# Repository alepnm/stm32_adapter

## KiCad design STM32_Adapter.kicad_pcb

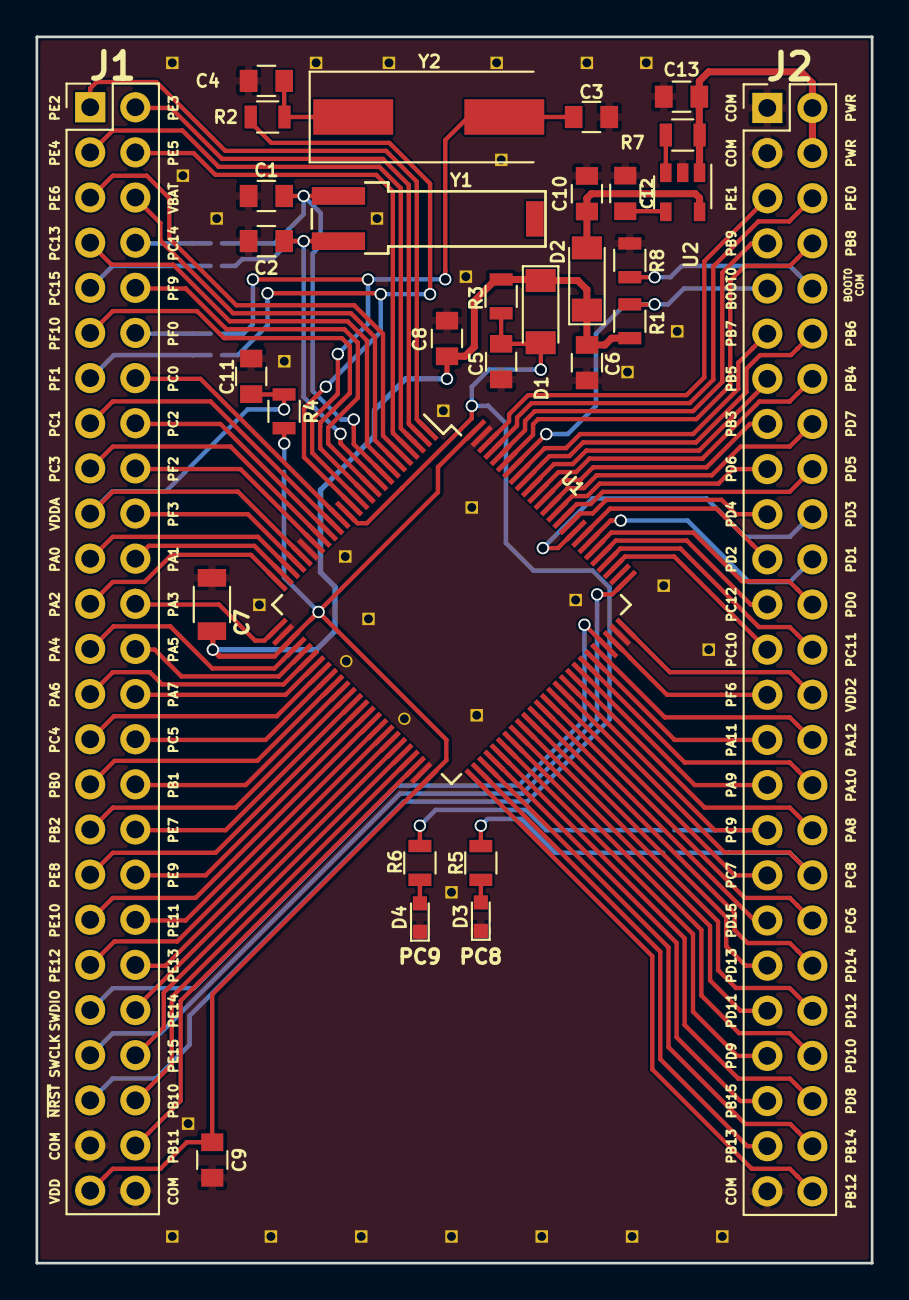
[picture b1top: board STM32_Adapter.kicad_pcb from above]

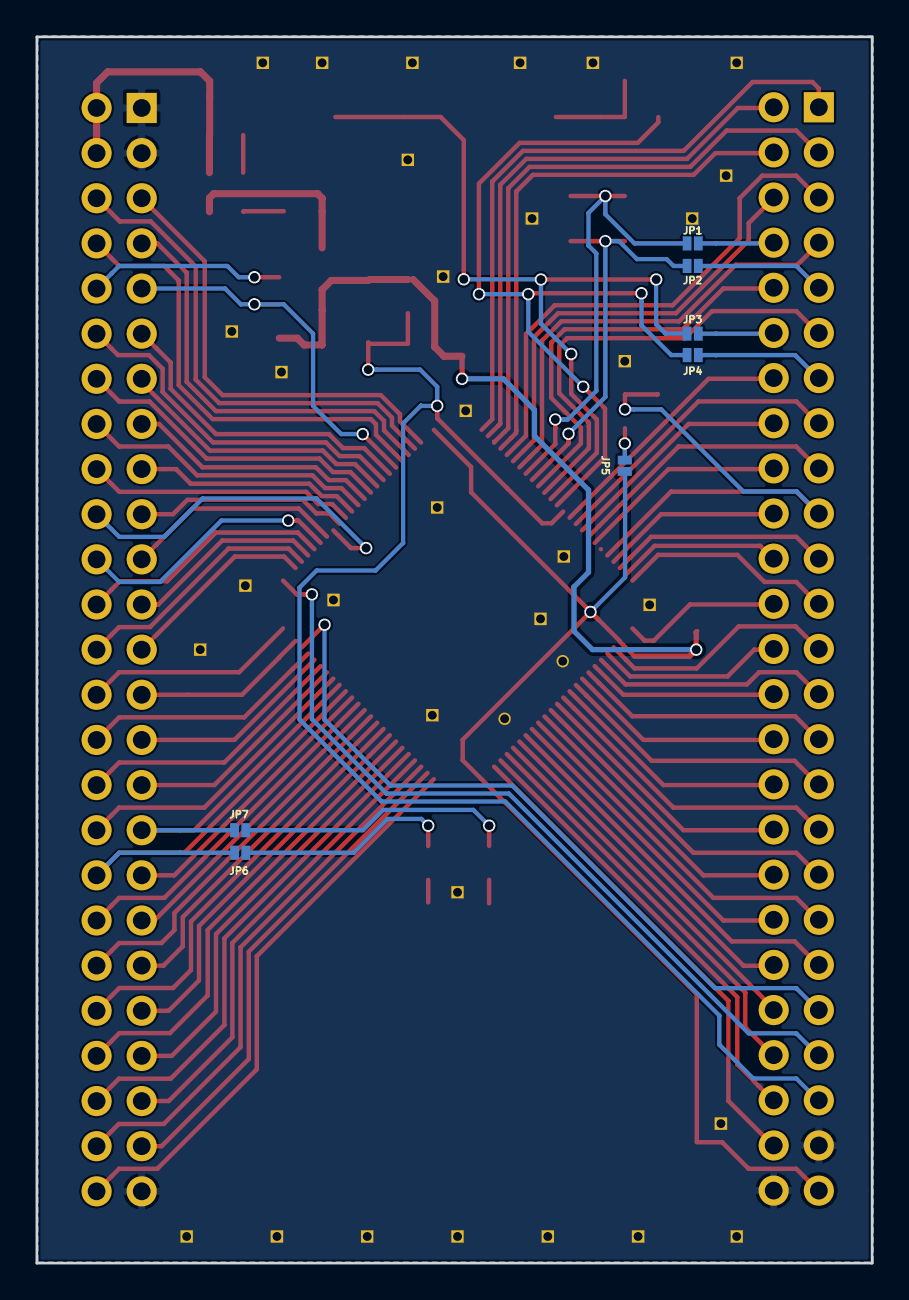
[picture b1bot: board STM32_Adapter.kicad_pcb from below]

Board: 2 copper layers, 47.0 x 69.0 mm, 38 parts (7 on the bottom side), 108 nets.

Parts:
C1, C2, C3, C4: C_22p_0805_X7R; C_0805
C5, C6, C8, C9, C10, C11, C12, C13: C_100n_0805_X7R; C_0805
C7: C_1u_0805_X7R; C_1206
D1: D_BAS32; D_MiniMELF
D2: D_BAS85; D_MiniMELF
D3, D4: EL19-21SYGC; LED_0603
J1, J2: PinHeader_02X25; Pin_Header_Straight_2x25_Pitch2.54mm
JP1, JP2, JP3, JP4, JP5, JP6, JP7: Jumper_SMD; SMD_Jumper
R1: R_10k_0805_1%; R_0805
R2: R_470_0805_1%; R_0805
R3: R_15k_0805_1%; R_0805
R4, R8: R_120_0805_1%; R_0805
R5, R6, R7: R_1k_0805_1%; R_0805
U1: STM32F072V8T6; LQFP-100_14x14mm_Pitch0.5mm
U2: SIP21106; SOT-23-5
Y1: Crystal_smd_32768_horizontal; Crystal_32768_horizontzl
Y2: Crystal_smd_11x5; Crystal_SMD_HC49-SD

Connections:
/BOOT0: J2.9, R1.2, U1.94
/COM: C1.2, C2.2, C3.2, C4.2, C5.2, C6.1, C7.2, C8.2, C9.2, C10.2, C11.2, C12.2, C13.2, D3.1, D4.1, J1.47, J1.50, J2.1, J2.3, J2.49, R8.2, U1.20, U1.27, U1.49, U1.74, U1.99, U2.2
/OSC32IN: C1.1, JP1.2, U1.8, Y1.2
/OSC32OUT: C2.1, JP2.2, U1.9, Y1.1
/PA0: J1.21, U1.23
/PA1: J1.22, U1.24
/PA2: J1.23, U1.25
/PA3: J1.24, U1.26
/PA4: J1.25, U1.29
/PA5: J1.26, U1.30
/PA6: J1.27, U1.31
/PA7: J1.28, U1.32
/PA8: J2.34, U1.67
/PA9: J2.31, U1.68
/PA10: J2.32, U1.69
/PA11: J2.29, U1.70
/PA12: J2.30, U1.71
/PB0: J1.31, U1.35
/PB1: J1.32, U1.36
/PB2: J1.33, U1.37
/PB3: J2.15, U1.89
/PB4: J2.14, U1.90
/PB5: J2.13, U1.91
/PB6: J2.12, U1.92
/PB7: J2.11, U1.93
/PB8: J2.8, U1.95
/PB9: J2.7, U1.96
/PB10: J1.46, U1.47
/PB11: J1.48, U1.48
/PB12: J2.50, U1.51
/PB13: J2.47, U1.52
/PB14: J2.48, U1.53
/PB15: J2.45, U1.54
/PC0: J1.14, U1.15
/PC1: J1.15, U1.16
/PC2: J1.16, U1.17
/PC3: J1.17, U1.18
/PC4: J1.29, U1.33
/PC5: J1.30, U1.34
/PC6: J2.38, U1.63
/PC7: J2.35, U1.64
/PC8: J2.36, JP6.1, U1.65
/PC9: J2.33, JP7.1, U1.66
/PC10: J2.25, U1.78
/PC11: J2.26, U1.79
/PC12: J2.23, U1.80
/PC13: J1.7, U1.7
/PC14: J1.8, JP1.1
/PC15: J1.9, JP2.1
/PD0: J2.24, U1.81
/PD1: J2.22, U1.82
/PD2: J2.21, U1.83
/PD3: J2.20, U1.84
/PD4: J2.19, U1.85
/PD5: J2.18, U1.86
/PD6: J2.17, U1.87
/PD7: J2.16, U1.88
/PD8: J2.46, U1.55
/PD9: J2.43, U1.56
/PD10: J2.44, U1.57
/PD11: J2.41, U1.58
/PD12: J2.42, U1.59
/PD13: J2.39, U1.60
/PD14: J2.40, U1.61
/PD15: J2.37, U1.62
/PE0: J2.6, U1.97
/PE1: J2.5, U1.98
/PE2: J1.1, U1.1
/PE3: J1.2, U1.2
/PE4: J1.3, U1.3
/PE5: J1.4, U1.4
/PE6: J1.5, U1.5
/PE7: J1.34, U1.38
/PE8: J1.35, U1.39
/PE9: J1.36, U1.40
/PE10: J1.37, U1.41
/PE11: J1.38, U1.42
/PE12: J1.39, U1.43
/PE13: J1.40, U1.44
/PE14: J1.42, U1.45
/PE15: J1.44, U1.46
/PF0: J1.12, JP3.1
/PF1: J1.13, JP4.1
/PF2: J1.18, U1.19
/PF3: J1.20, U1.22
/PF6: J2.27, U1.73
/PF9: J1.10, U1.10
/PF10: J1.11, U1.11
/PWR: C13.1, J2.2, J2.4, R7.2, U2.1
/RCCIN: C3.1, JP3.2, U1.12, Y2.2
/RCCOUT: JP4.2, R2.1, U1.13
/SWCLK: J1.43, U1.76
/SWDIO: J1.41, U1.72
/VBAT: J1.6, U1.6
/VDD: C6.2, C7.1, C8.1, C9.1, D1.1, D2.1, J1.49, JP5.1, R1.1, R3.2, U1.28, U1.50, U1.100
/VDDA: C11.1, J1.19, R4.2, U1.21
/VDDIO2: J2.28, U1.75
/~NRST: C5.1, D1.2, J1.45, R3.1, U1.14
unnamed: C4.1, R2.2, Y2.1
unnamed: C10.1, D2.2, U2.5
unnamed: C12.1, U2.4
unnamed: D3.2, R5.2
unnamed: D4.2, R6.2
unnamed: J2.10, R8.1
unnamed: JP5.2, R4.1
unnamed: JP6.2, R5.1
unnamed: JP7.2, R6.1
unnamed: R7.1, U2.3

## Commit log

2017-08-11 inicializavimas
2017-08-12 pcb plokstes paruosimas
2017-08-14 pcb plokstes proektavimas
2017-09-11 smulkus pcb plokstes pakeitimai
